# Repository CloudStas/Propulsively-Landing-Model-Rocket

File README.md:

# Sliverflame, Propulsively Landing Model Rocket Using TVC

## What is this?
Sliverflame is an active-stability model rocket designed to achieve vertical, propulsive landings using standard hobby rocket motors. This project is inspired by BPS space, when he landed his model rocket, Scout F. Additionally, I am doing this for stardance(stardance.hackclub.com/).

## How does it work?
1. Dual-Motors config, The rocket engine mount holds two motors sequentially. The upper landing motor is securely housed completely inside the body tube. The lower ascent motor sits partially inserted (~5mm) into the bottom of the tube.
2. Thrust based seperation, Once the ascent motor burns out, the top landing motor is ignited and it pushes the ascent motor in a different direction and then immediately the rocket stabilizes.

## Progress
I have finished design for all of the parts I just need to also 3D print them and I also with the budget of about $600 I can also laser cut landing legs. I am using PETG for the TVC gimbal and for the rest I am using regular PLA.

## Hardware
Look into the files for the parts in this directory or you can check it out in onshape: https://cad.onshape.com/documents/642eb1595bbfbb88e3413de9/w/294c2c178315e1ad00baf07d/e/72f61137f22d9a471da72dad.

Also I didn't go with a PCB because it was like $308 and it is way cheaper to just wire everything physically with wires instead on a PCB. But if you do want to check out the PCB it's in Kicad/ and gerbers.zip in Production/

Here is a shorted BOM list you can also check out the longer one in Rocket_BOM.csv:

| **Item / Category** | **Cost** | **Source** |
| :--- | :--- | :--- |
| **Estes F15 Rocket Motors (8-pack)** | $110.00 | Local Hobby Store |
| **SPARKHOBBY ES3352 Servos** | $48.28 | Amazon |
| **Custom Laser Cut Throttle Arms** | $32.66 | SendCutSend |
| **HOOVO 2S Shorty Lipo Batteries (2-pack)** | $34.43 | Amazon |
| **UHT Carbon Fiber Rods** | $25.69 | Amazon |
| **Avionics & Electronics** (ESP32-S3, MPU6050, BMP280, MOSFETs, UBECs) | $96.82 | Amazon |
| **Hardware & Miscellaneous** (Filament, Connectors, Wires, Fuses, Bag, Charger) | $162.93 | Amazon |
| **Structural Consumables** (Nichrome wire, Kraft paper, Rods, Glue, Bands) | $37.45 | Amazon |
| **Total** | **$548.26** | |

## Software
/Production/Software/ for all the software on the rocket. This rocket will be using Arduino IDE to program it. More info will come when I finish the software. My plan for the software is when the computer turns on it goes into a waiting loop and waits until my launch controller(which is also an ESP32) sends a signal to arm the rocket. The rocket then enters in a arm loop. it waits for the launch button to be pressed at the same time as the arm button, once it does it sends ignition to the first rocket motor, and when there is acceleration spike, it changes the variable motor1igntiontrue and then, It enters a Flight Loop. In the Flight loop it will use some math and the IMU gyroscope data, to see if the rocket is about to tilt over, if it is change the TVC orienatation to an opposite of the direction it's falling for a slight bit to get it back to stable, continuing to do those readjustments until the first motor burns out. It check's if the rocket is fine like if it crashed or if something else happened if did it will abort the flight and just fall (not that high). For the landing part is that it will ignite the top motor (landing motor) to push out the ascent motor and the TVC mount to angle one direction for just a bit and then re-stabilize immediately. Final part is just using the TVC loop and once it almost reaches the ground, throttle the motor (or also throttle it at the spike of the burn to prevent the rocket from going up). And finally then deploy landing legs via the nichrome wire and rubber band by burning it and then landing (hopefully).
 
## Safety Stuff
Since the rocket motor inside the tube can melt the TVC_Tube I am going to add some kraft paper inside so even if the exhaust touches inside the tube it will actually burn the paper and the throttle arms are made from Steel 1008 so I think its good. Additionally, I added software and hardware arming for the rocket motor, and I have to press both the Launch and Arm button to launch, so there is no way for me to accidentantly to ignite it.  

You can use this project however you'd like.

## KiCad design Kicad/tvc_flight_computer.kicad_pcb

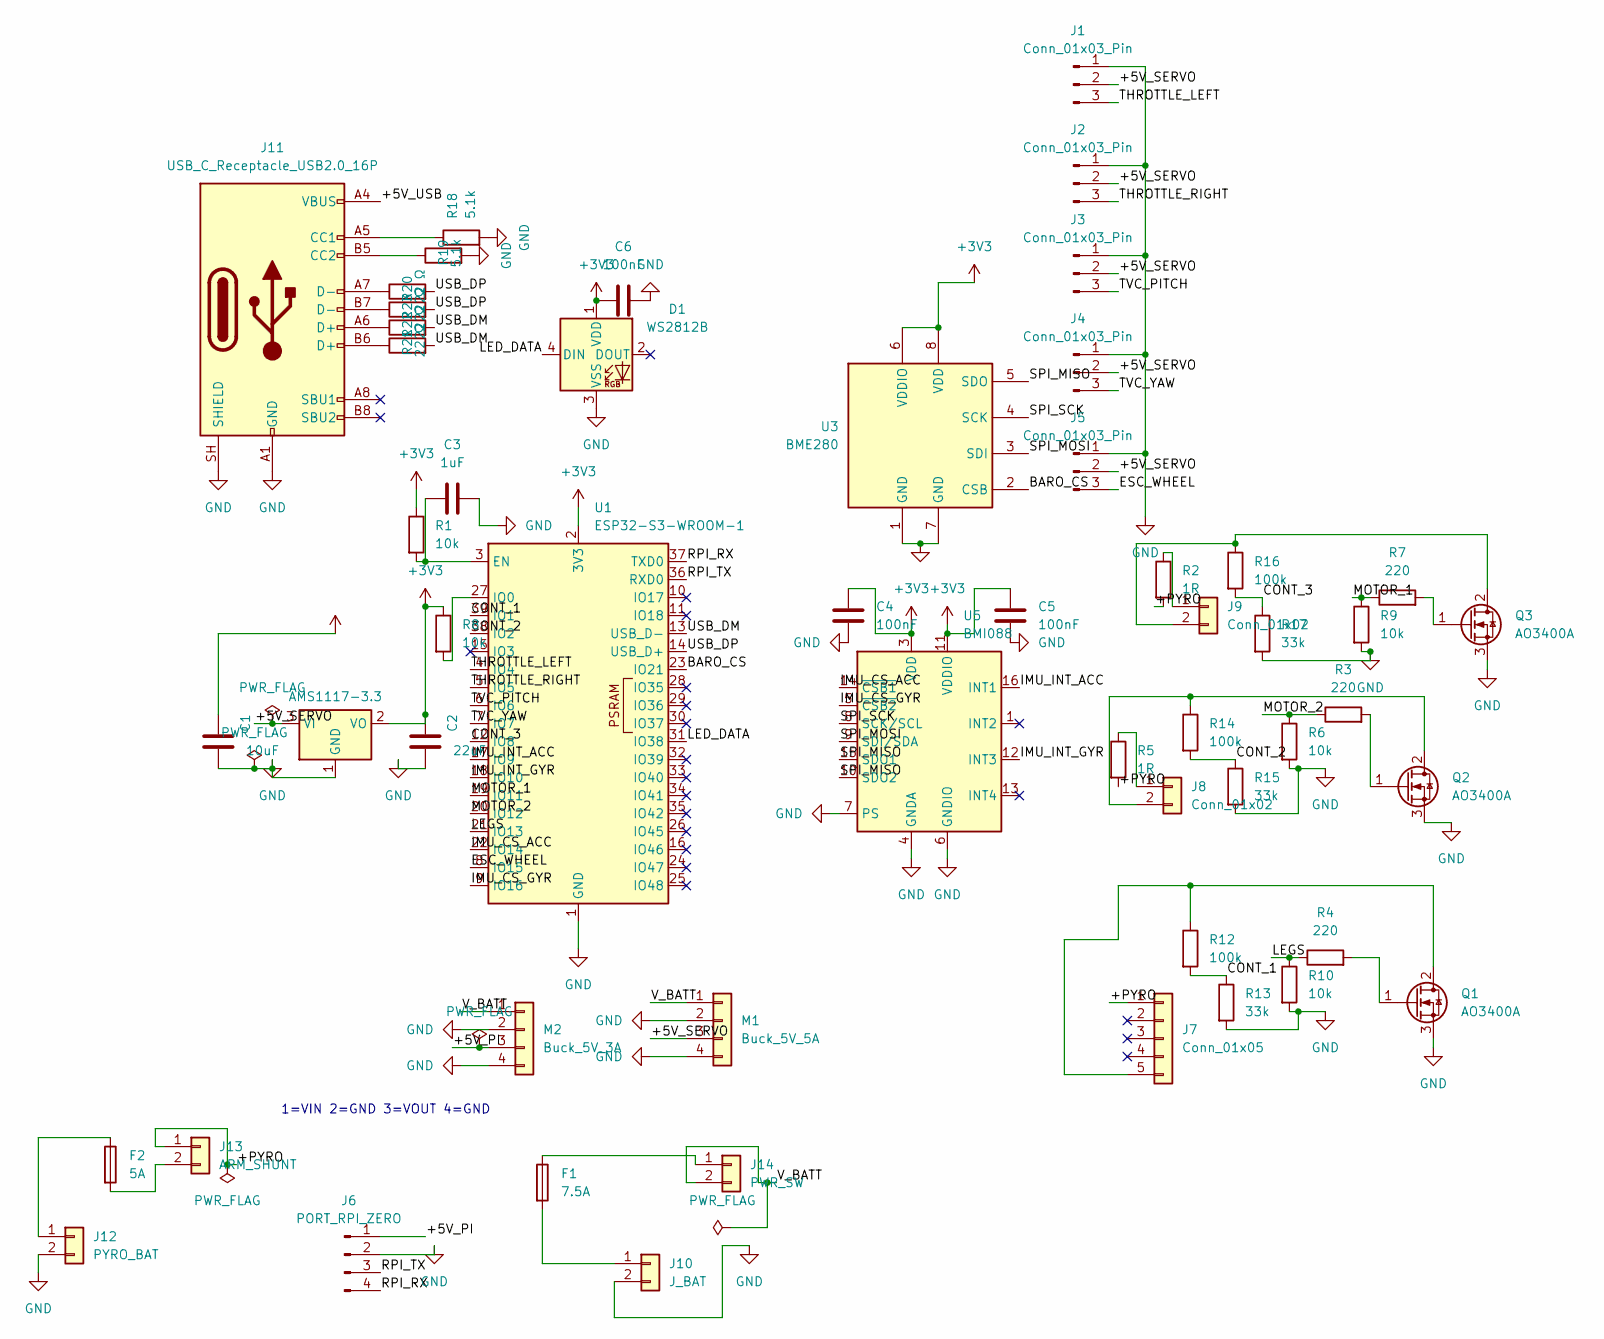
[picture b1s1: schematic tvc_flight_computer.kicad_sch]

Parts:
C1: 10uF; C_0603_1608Metric
C2: 22uF; C_0603_1608Metric
C3: 1uF; C_0603_1608Metric
C4, C5, C6: 100nF; C_0603_1608Metric
D1: WS2812B; LED_WS2812B_PLCC4_5.0x5.0mm_P3.2mm; LCSC C2843785
F1: 7.5A; Fuse_1206_3216Metric
F2: 5A; Fuse_1206_3216Metric
J1, J2, J3, J4, J5: Conn_01x03_Pin; PinHeader_1x03_P2.54mm_Vertical
J6: PORT_RPI_ZERO; PinHeader_1x04_P2.54mm_Vertical
J7: Conn_01x05; PinHeader_1x05_P2.54mm_Vertical
J8, J9: Conn_01x02; PinHeader_1x02_P2.54mm_Vertical
J10: J_BAT; PinHeader_1x02_P2.54mm_Vertical
J11: USB_C_Receptacle_USB2.0_16P; USB_C_Receptacle_HRO_TYPE-C-31-M-12; LCSC C165948
J12: PYRO_BAT; PinHeader_1x02_P2.54mm_Vertical
J13: ARM_SHUNT; PinHeader_1x02_P2.54mm_Vertical
J14: PWR_SW; PinHeader_1x02_P2.54mm_Vertical
M1: Buck_5V_5A; PinHeader_1x04_P2.54mm_Vertical
M2: Buck_5V_3A; PinHeader_1x04_P2.54mm_Vertical
Q1, Q2, Q3: AO3400A; SOT-23; LCSC C20917
R1, R6, R8, R9, R10: 10k; R_0603_1608Metric
R2, R5: 1R; R_2512_6332Metric
R3, R4, R7: 220; R_0603_1608Metric
R12, R14, R16: 100k; R_0603_1608Metric
R13, R15, R17: 33k; R_0603_1608Metric
R18, R19: 5.1k; R_0603_1608Metric
R20, R21, R22, R23: 22 Ω; R_0603_1608Metric
U1: ESP32-S3-WROOM-1; LCSC C2913202
U2: AMS1117-3.3; SOT-223-3_TabPin2
U3: BME280; Bosch_LGA-8_2.5x2.5mm_P0.65mm_ClockwisePinNumbering; LCSC C92489
U5: BMI088; Bosch_LGA-16_4.5x3mm_P0.5mm_LayoutBorder7x1y_ClockwisePinNu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; LCSC C194919

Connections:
+3V3: C1.1, C2.1, C4.1, C5.1, C6.1, D1.1 (VDD), R1.1, R8.1, U1.2 (3V3), U2.2 (VO), U3.6 (VDDIO), U3.8 (VDD), U5.3 (VDD), U5.11 (VDDIO)
/+5V_PI: J6.1, M2.3
/+5V_SERVO: J1.2, J2.2, J3.2, J4.2, J5.2, M1.3, U2.3 (VI)
/+5V_USB: J11.A4 (VBUS), J11.A9 (VBUS), J11.B4 (VBUS), J11.B9 (VBUS)
/+PYRO: J7.1, J13.1, R2.2, R5.2
/BARO_CS: U1.23 (IO21), U3.2 (CSB)
/CONT_1: R12.2, R13.1, U1.39 (IO1)
/CONT_2: R14.2, R15.1, U1.38 (IO2)
/CONT_3: R16.2, R17.1, U1.12 (IO8)
/ESC_WHEEL: J5.3, U1.8 (IO15)
/IMU_CS_ACC: U1.22 (IO14), U5.14 (~CSB1)
/IMU_CS_GYR: U1.9 (IO16), U5.5 (~CSB2)
/IMU_INT_ACC: U1.17 (IO9), U5.16 (INT1)
/IMU_INT_GYR: U1.18 (IO10), U5.12 (INT3)
/LED_DATA: D1.4 (DIN), U1.31 (IO38)
/LEGS: R4.1, R10.1, U1.21 (IO13)
/MOTOR_1: R7.1, R9.1, U1.19 (IO11)
/MOTOR_2: R3.1, R6.1, U1.20 (IO12)
/RPI_RX: J6.4, U1.37 (TXD0)
/RPI_TX: J6.3, U1.36 (RXD0)
/SPI_MISO: U3.5 (SDO), U5.10 (SDO2), U5.15 (SDO1)
/SPI_MOSI: U3.3 (SDI), U5.9 (SDI/SDA)
/SPI_SCK: U3.4 (SCK), U5.8 (SCK/SCL)
/THROTTLE_LEFT: J1.3, U1.4 (IO4)
/THROTTLE_RIGHT: J2.3, U1.5 (IO5)
/TVC_PITCH: J3.3, U1.6 (IO6)
/TVC_YAW: J4.3, U1.7 (IO7)
/USB_DM: R21.2, R22.2, U1.13 (USB_D-)
/USB_DP: R20.2, R23.2, U1.14 (USB_D+)
/V_BATT: J14.2, M1.1, M2.1
GND: C1.2, C2.2, C3.2, C4.2, C5.2, C6.2, D1.3 (VSS), J1.1, J2.1, J3.1, J4.1, J5.1, J6.2, J10.2, J11.A1 (GND), J11.A12 (GND), J11.B1 (GND), J11.B12 (GND), J11.SH (SHIELD), J12.2, M1.2, M1.4, M2.2, M2.4, Q1.3 (S), Q2.3 (S), Q3.3 (S), R6.2, R9.2, R10.2, R13.2, R15.2, R17.2, R18.2, R19.2, U1.1 (GND), U1.40 (GND), U1.41 (GND), U2.1 (GND), U3.1 (GND), U3.7 (GND), U5.2 (GNDA), U5.4 (GNDA), U5.6 (GNDIO), U5.7 (PS)
unnamed: J7.5, Q1.2 (D), R12.1
unnamed: J8.1, R5.1
unnamed: J8.2, Q2.2 (D), R14.1
unnamed: J9.1, R2.1
unnamed: J9.2, Q3.2 (D), R16.1
unnamed: F1.2, J10.1
unnamed: J11.A5 (CC1), R18.1
unnamed: J11.B5 (CC2), R19.1
unnamed: J11.A6 (D+), R22.1
unnamed: J11.B6 (D+), R21.1
unnamed: J11.A7 (D-), R20.1
unnamed: J11.B7 (D-), R23.1
unnamed: F2.1, J12.1
unnamed: F2.2, J13.2
unnamed: F1.1, J14.1
unnamed: Q1.1 (G), R4.2
unnamed: Q2.1 (G), R3.2
unnamed: Q3.1 (G), R7.2
unnamed: C3.1, R1.2, U1.3 (EN)
unnamed: R8.2, U1.27 (IO0)

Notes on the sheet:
1=VIN 2=GND 3=VOUT 4=GND

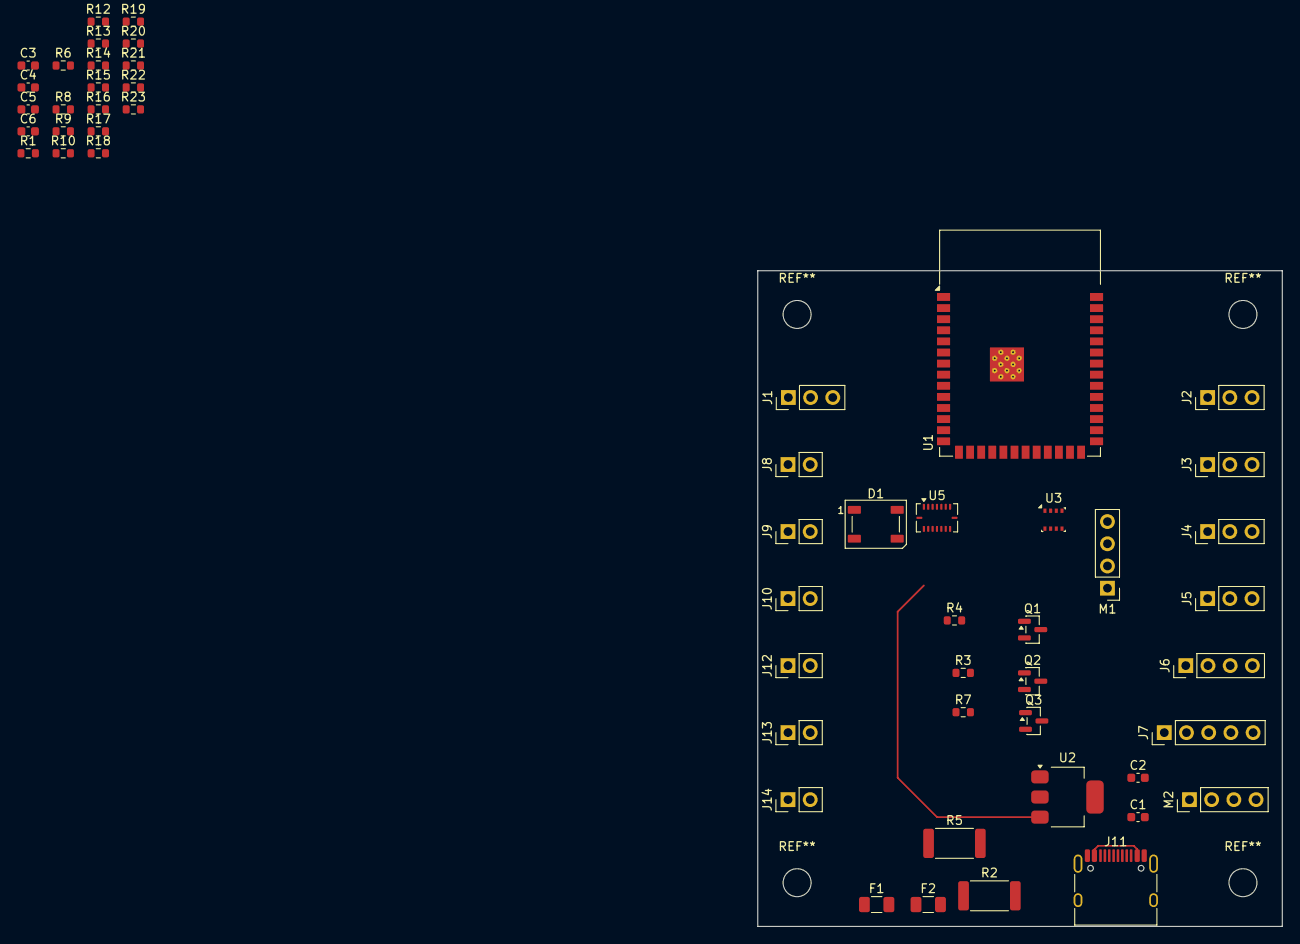
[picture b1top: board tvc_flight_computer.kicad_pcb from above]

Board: 4 copper layers, 60.0 x 75.0 mm, 54 parts (0 on the bottom side), 51 nets.
